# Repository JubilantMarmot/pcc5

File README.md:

# Cool card PCB

This is my first PCB project. It took me around 20 hours.
It is a small Linux computer that is the size of a business card. Based off of Allwinner F1C200s.

Around $5 or so per card? It is not too bad.

## 3d render

To print, make sure that you select 2-layer PCB.

## Schematic

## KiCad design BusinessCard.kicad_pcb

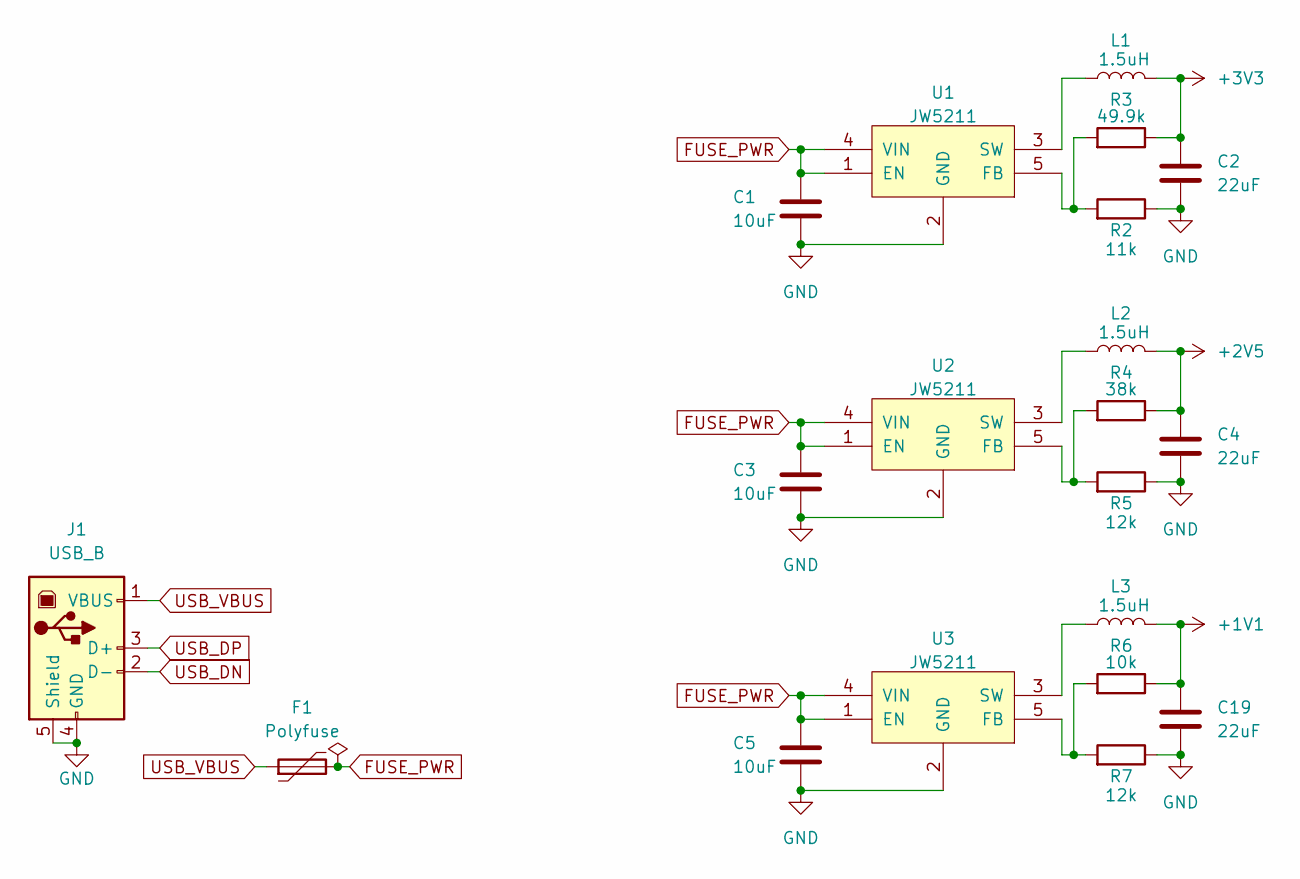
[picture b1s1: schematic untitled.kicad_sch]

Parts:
C1, C3, C5: 10uF; C_0201_0603Metric
C2, C4, C19: 22uF; C_0201_0603Metric
F1: Polyfuse; Fuse_0603_1608Metric
J1: USB_B; USB_A_CNCTech_1001-011-01101_Horizontal
L1, L2, L3: 1.5uH; L_0201_0603Metric
R2: 11k; R_0201_0603Metric
R3: 49.9k; R_0201_0603Metric
R4: 38k; R_0201_0603Metric
R5, R7: 12k; R_0201_0603Metric
R6: 10k; R_0201_0603Metric
U1, U2, U3: JW5211; SOT-23-5

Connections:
+1V1: C19.2, L3.2, R6.1; also elsewhere on the board
+2V5: C4.2, L2.2, R4.1; also elsewhere on the board
+3V3: C2.2, L1.2, R3.1; also elsewhere on the board
FUSE_PWR: C1.1, C3.1, C5.1, F1.2, U1.1 (EN), U1.4 (VIN), U2.1 (EN), U2.4 (VIN), U3.1 (EN), U3.4 (VIN)
GND: C1.2, C2.1, C3.2, C4.1, C5.2, C19.1, J1.4 (GND), J1.5 (Shield), R2.1, R5.1, R7.1, U1.2 (GND), U2.2 (GND), U3.2 (GND); also elsewhere on the board
unnamed: R2.2, R3.2, U1.5 (FB)
unnamed: L1.1, U1.3 (SW)
unnamed: R4.2, R5.2, U2.5 (FB)
unnamed: L2.1, U2.3 (SW)
unnamed: R6.2, R7.2, U3.5 (FB)
unnamed: L3.1, U3.3 (SW)
USB_DN: J1.2 (D-); also elsewhere on the board
USB_DP: J1.3 (D+); also elsewhere on the board
USB_VBUS: F1.1, J1.1 (VBUS)

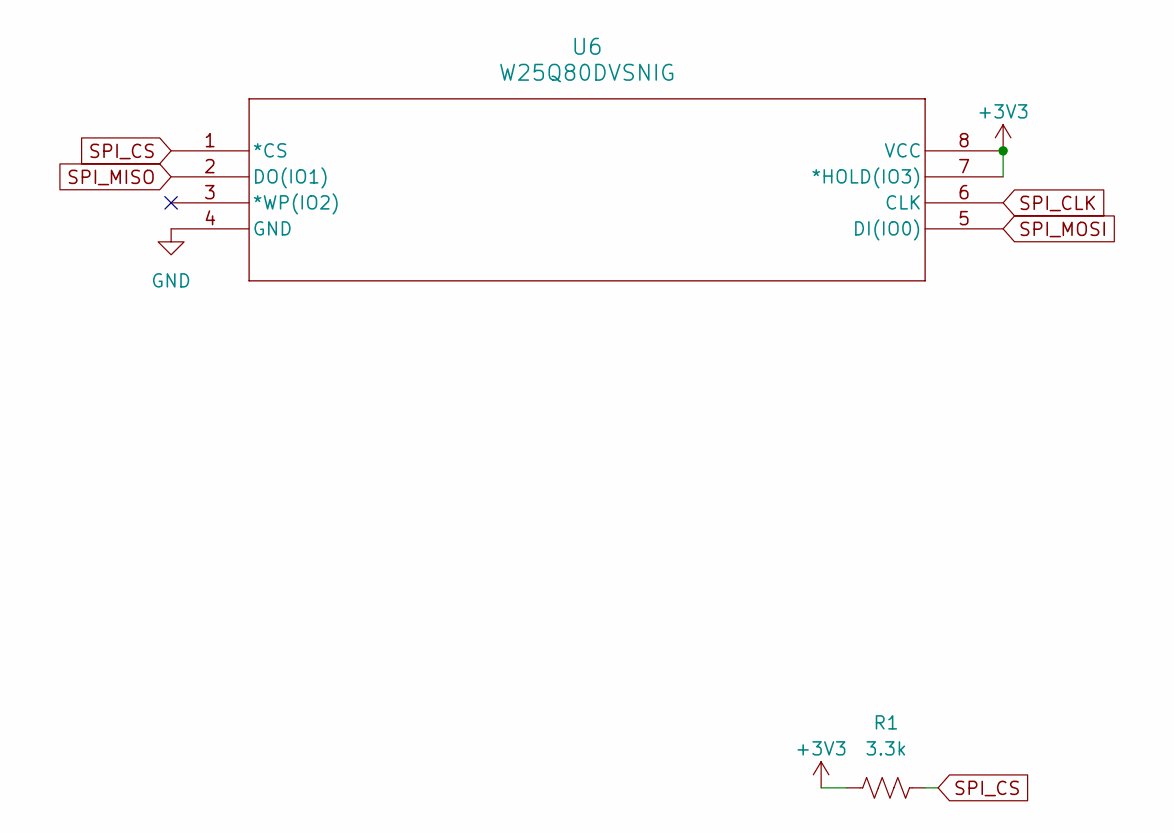
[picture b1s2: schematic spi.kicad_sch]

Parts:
R1: 3.3k; R_0201_0603Metric
U6: W25Q80DVSNIG; WIN_SN-8_WIN

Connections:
+3V3: R1.2, U6.7 (*HOLD(IO3)), U6.8 (VCC); also elsewhere on the board
GND: U6.4 (GND); also elsewhere on the board
SPI_CLK: U6.6 (CLK); also elsewhere on the board
SPI_CS: R1.1, U6.1 (*CS); also elsewhere on the board
SPI_MISO: U6.2 (DO(IO1)); also elsewhere on the board
SPI_MOSI: U6.5 (DI(IO0)); also elsewhere on the board

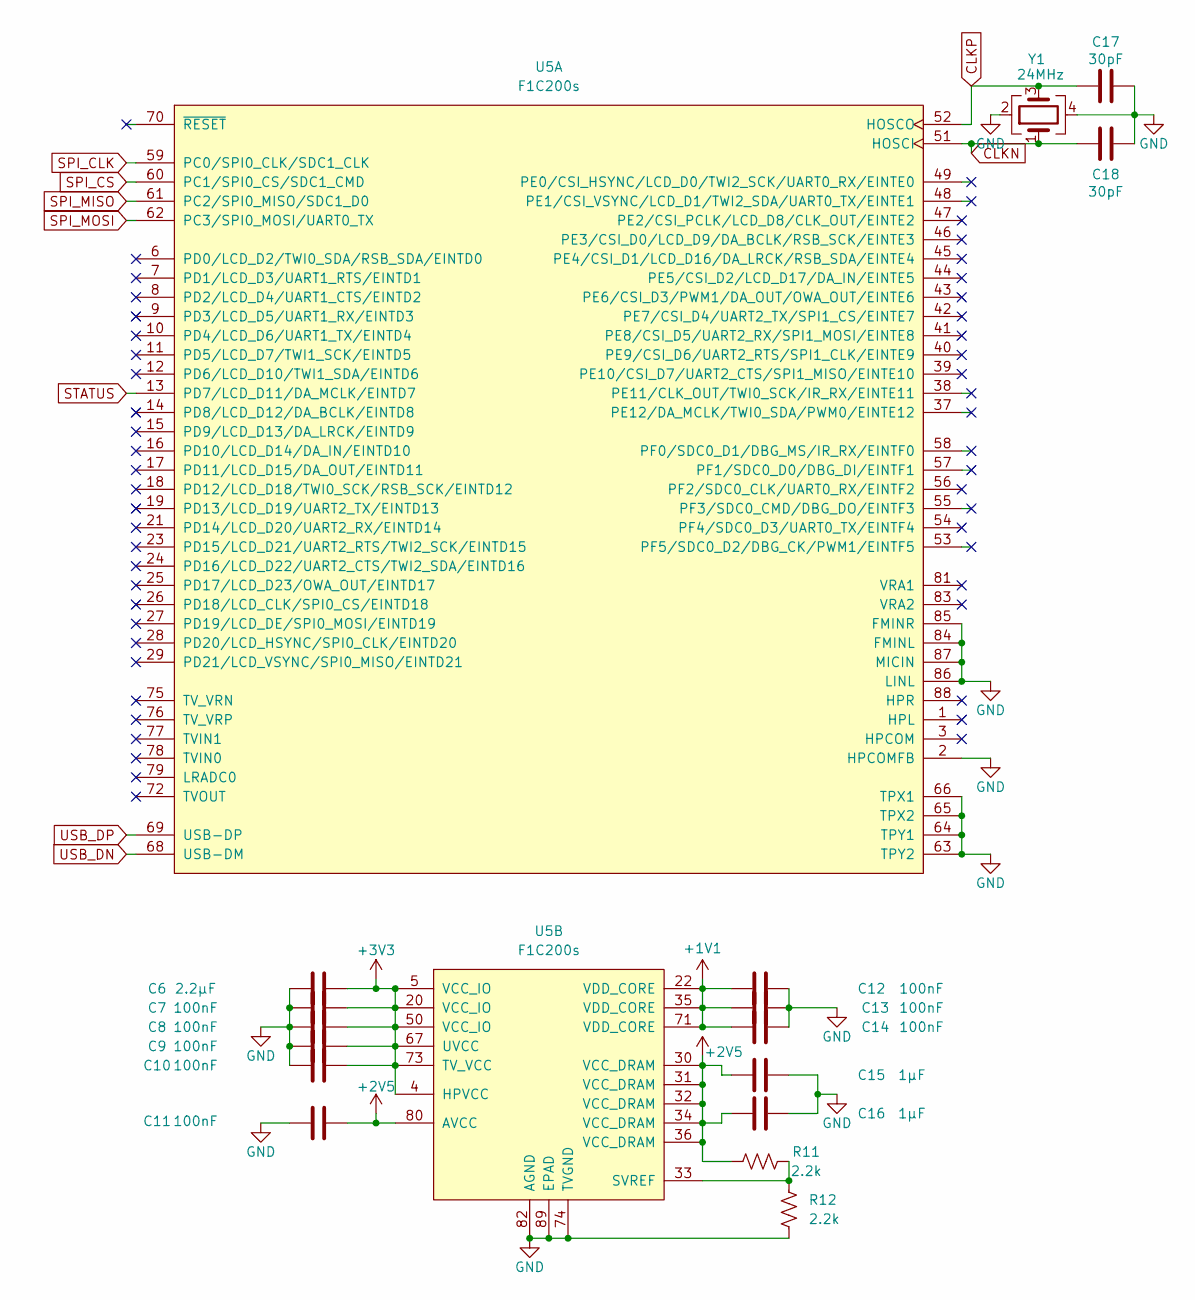
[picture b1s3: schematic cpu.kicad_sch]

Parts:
C6: 2.2µF; C_0201_0603Metric
C7, C8, C9, C10, C11, C12, C13, C14: 100nF; C_0201_0603Metric
C15, C16: 1µF; C_0201_0603Metric
C17, C18: 30pF; C_0201_0603Metric
R11, R12: 2.2k; R_0201_0603Metric
U5: F1C200s; QFN-88_EP_10x10_Pitch0.4mm
Y1: 24MHz; Oscillator_SMD_TXC_7C-4Pin_5.0x3.2mm

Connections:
+1V1: C12.1, C13.1, C14.1, U5.22 (VDD_CORE), U5.35 (VDD_CORE), U5.71 (VDD_CORE); also elsewhere on the board
+2V5: C11.2, C15.1, C16.1, R11.1, U5.30 (VCC_DRAM), U5.31 (VCC_DRAM), U5.32 (VCC_DRAM), U5.34 (VCC_DRAM), U5.36 (VCC_DRAM), U5.80 (AVCC); also elsewhere on the board
+3V3: C6.2, C7.2, C8.2, C9.2, C10.2, U5.4 (HPVCC), U5.5 (VCC_IO), U5.20 (VCC_IO), U5.50 (VCC_IO), U5.67 (UVCC), U5.73 (TV_VCC); also elsewhere on the board
CLKN: C18.1, U5.51 (HOSCI), Y1.1
CLKP: C17.1, U5.52 (HOSCO), Y1.3
GND: C6.1, C7.1, C8.1, C9.1, C10.1, C11.1, C12.2, C13.2, C14.2, C15.2, C16.2, C17.2, C18.2, R12.2, U5.2 (HPCOMFB), U5.63 (TPY2), U5.64 (TPY1), U5.65 (TPX2), U5.66 (TPX1), U5.74 (TVGND), U5.82 (AGND), U5.84 (FMINL), U5.85 (FMINR), U5.86 (LINL), U5.87 (MICIN), U5.89 (EPAD), Y1.2, Y1.4; also elsewhere on the board
unnamed: R11.2, R12.1, U5.33 (SVREF)
SPI_CLK: U5.59 (PC0/SPI0_CLK/SDC1_CLK); also elsewhere on the board
SPI_CS: U5.60 (PC1/SPI0_CS/SDC1_CMD); also elsewhere on the board
SPI_MISO: U5.61 (PC2/SPI0_MISO/SDC1_D0); also elsewhere on the board
SPI_MOSI: U5.62 (PC3/SPI0_MOSI/UART0_TX); also elsewhere on the board
STATUS: U5.13 (PD7/LCD_D11/DA_MCLK/EINTD7)
USB_DN: U5.68 (USB-DM); also elsewhere on the board
USB_DP: U5.69 (USB-DP); also elsewhere on the board

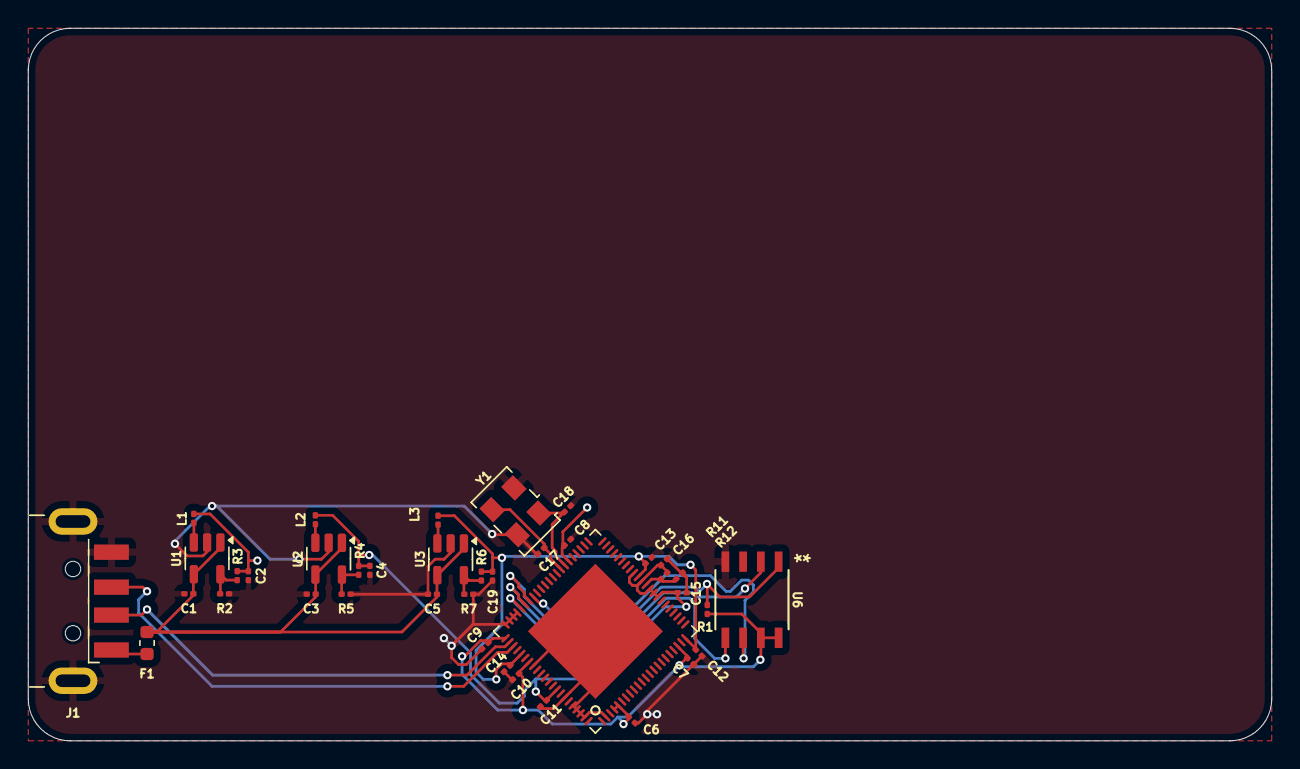
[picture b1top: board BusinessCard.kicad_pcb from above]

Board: 2 copper layers, 89.0 x 51.0 mm, 39 parts (0 on the bottom side), 21 nets.

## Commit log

2024-08-20 data
2024-08-21 progres
2024-08-21 progress
2024-08-22 progressa
